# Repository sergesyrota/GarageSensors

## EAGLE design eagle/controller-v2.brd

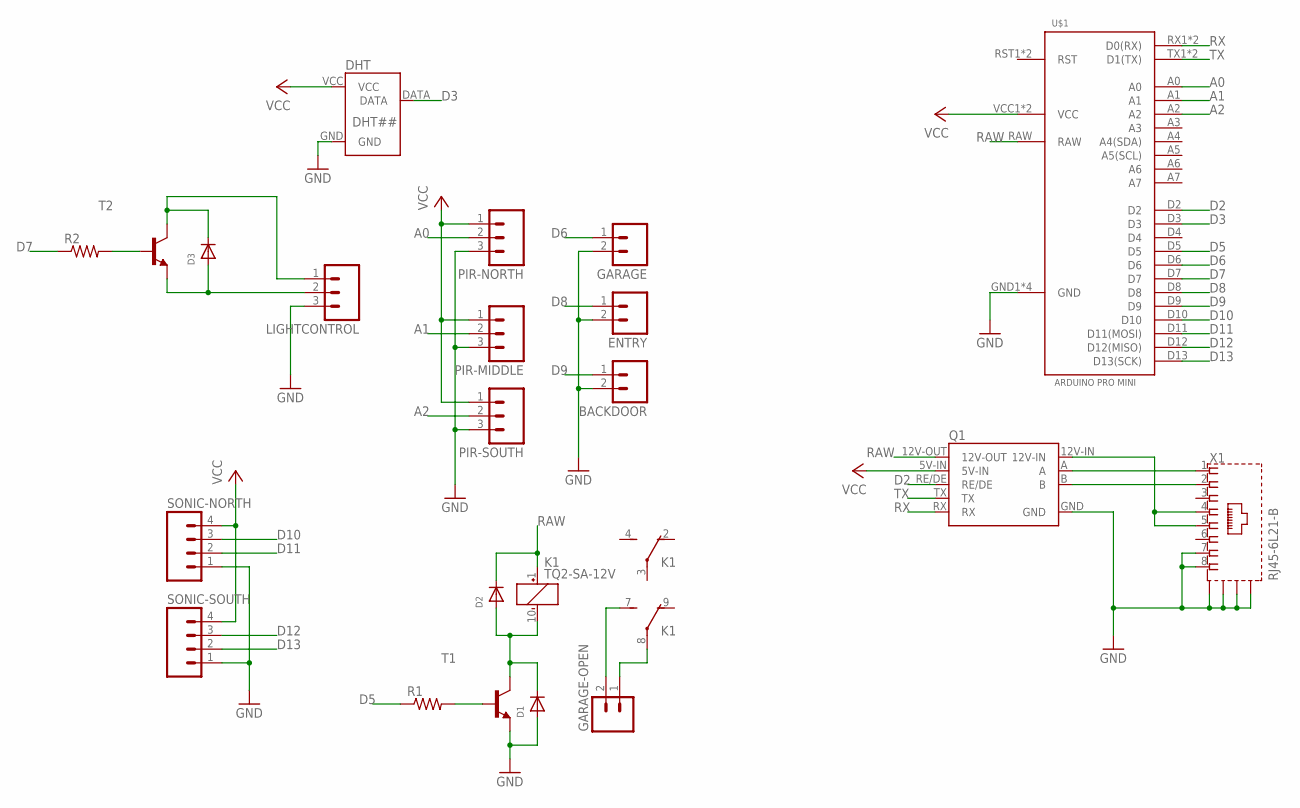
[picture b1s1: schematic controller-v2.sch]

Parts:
BACKDOOR: M02; 02P
D1, D2, D3: DIODESMA; SMADIODE
DHT: DHT##; CONNECTOR-4-PIN-0.1
ENTRY: M02; 02P
GARAGE: M02; 02P
GARAGE-OPEN: M02; 02P
K1: TQ2-SA-12V; TQ-SA
LIGHTCONTROL: M03; 03P
PIR-MIDDLE: M03; 03P
PIR-NORTH: M03; 03P
PIR-SOUTH: M03; 03P
Q1: RS485-ADAPTER0.05-CONNECTOR; RS485-ADAPTOR-05
R1, R2: R-US_R0603; R0603
SONIC-NORTH: M04; 04P
SONIC-SOUTH: M04; 04P
T1, T2: BC808-NPN-SOT23-BEC; SOT23-BEC
U$1: ARDUINO-PRO-MINI
X1: RJ45-6L21-B; RJ45-SHIELD1

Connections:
A0: PIR-NORTH.2, U$1.A0
A1: PIR-MIDDLE.2, U$1.A1
A2: PIR-SOUTH.2, U$1.A2
D2: Q1.RE/DE, U$1.D2
D3: DHT.DATA, U$1.D3
D5: R1.1, U$1.D5
D6: GARAGE.1, U$1.D6
D7: R2.1, U$1.D7
D8: ENTRY.1, U$1.D8
D9: BACKDOOR.1, U$1.D9
D10: SONIC-NORTH.3, U$1.D10
D11: SONIC-NORTH.2, U$1.D11 (D11(MOSI))
D12: SONIC-SOUTH.3, U$1.D12 (D12(MISO))
D13: SONIC-SOUTH.2, U$1.D13 (D13(SCK))
GND: BACKDOOR.2, D1.A, DHT.GND, ENTRY.2, GARAGE.2, LIGHTCONTROL.3, PIR-MIDDLE.3, PIR-NORTH.3, PIR-SOUTH.3, Q1.GND, SONIC-NORTH.1, SONIC-SOUTH.1, T1.E, U$1.GND1 (GND), U$1.GND2 (GND), U$1.GND3 (GND), U$1.GND4 (GND), X1.7, X1.8, X1.S1 (S), X1.S2 (S), X1.S3 (S), X1.S4 (S)
unnamed: D3.A, LIGHTCONTROL.2, T2.E
unnamed: Q1.12V-IN, X1.4, X1.5
unnamed: GARAGE-OPEN.1, K1.8
unnamed: Q1.A, X1.1
unnamed: Q1.B, X1.2
unnamed: GARAGE-OPEN.2, K1.7 (S)
unnamed: D1.C, D2.A, K1.10 (-), T1.C
unnamed: R1.2, T1.B
unnamed: D3.C, LIGHTCONTROL.1, T2.C
unnamed: R2.2, T2.B
RAW: D2.C, K1.1 (+), Q1.12V-OUT, U$1.RAW
RX: Q1.RX, U$1.RX1 (D0(RX)), U$1.RX2 (D0(RX))
TX: Q1.TX, U$1.TX1 (D1(TX)), U$1.TX2 (D1(TX))
VCC: DHT.VCC, PIR-MIDDLE.1, PIR-NORTH.1, PIR-SOUTH.1, Q1.5V-IN, SONIC-NORTH.4, SONIC-SOUTH.4, U$1.VCC1 (VCC), U$1.VCC2 (VCC)

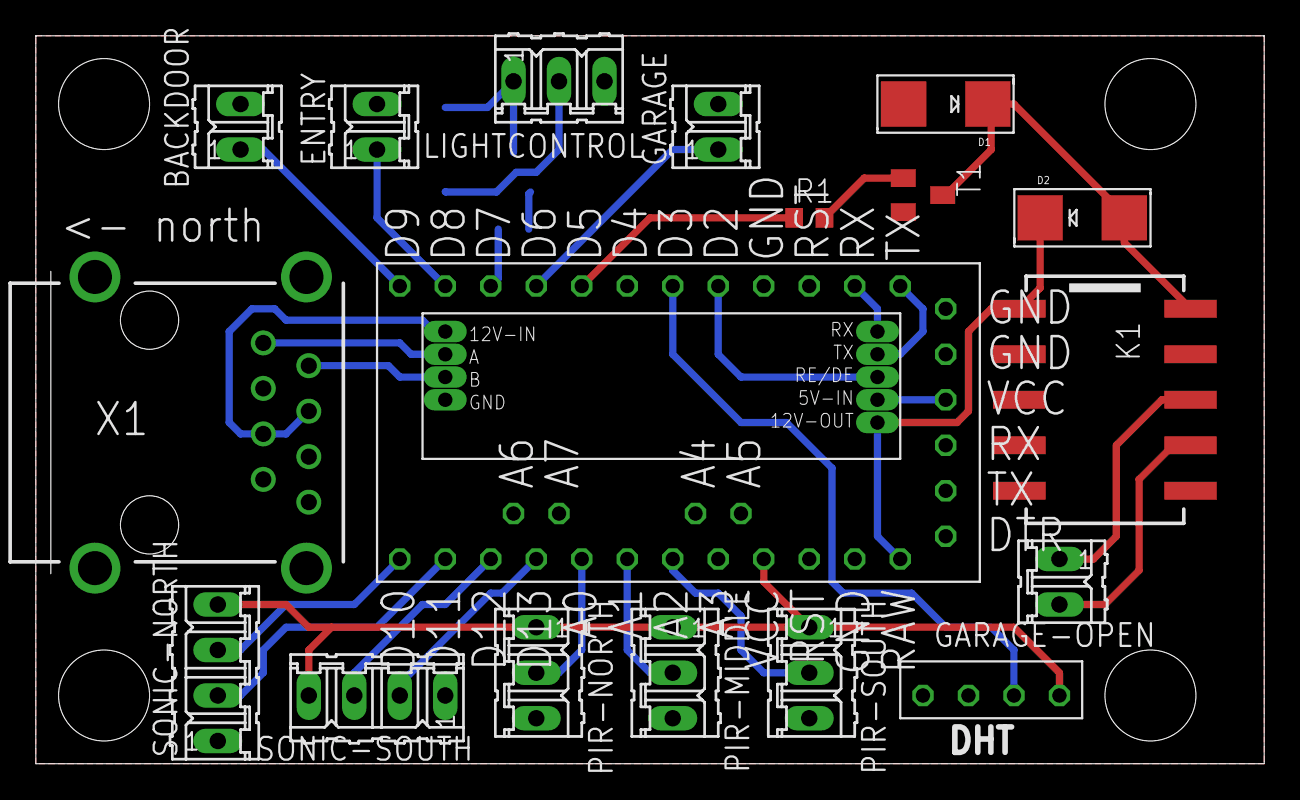
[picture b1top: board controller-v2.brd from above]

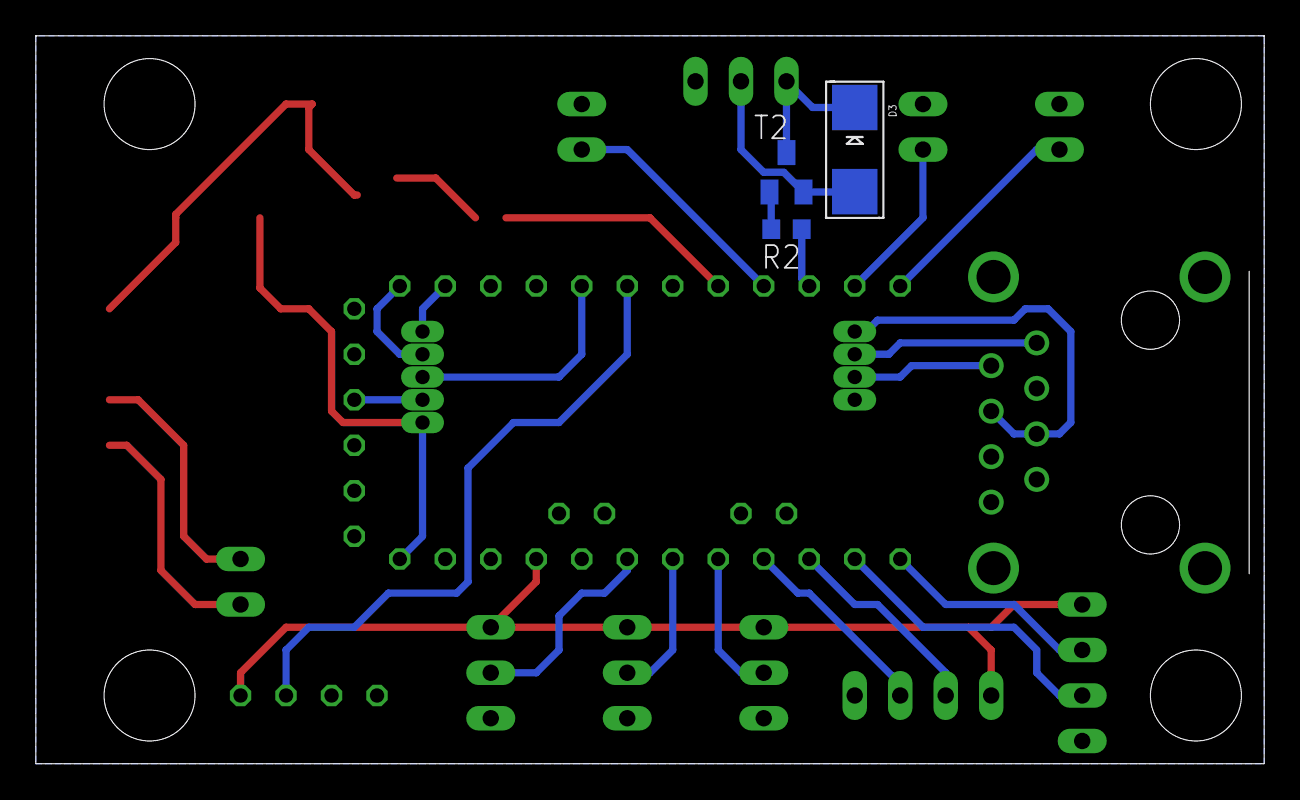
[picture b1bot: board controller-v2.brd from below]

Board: 2 copper layers, 68.6 x 40.6 mm, 22 parts (3 on the bottom side), 29 nets.

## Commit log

2016-12-03 Finalized garage sensors project, and installed.
2016-12-04 Fixed inverted door open/close check; Fixed setting motion lights timeout with int vs long conversion
